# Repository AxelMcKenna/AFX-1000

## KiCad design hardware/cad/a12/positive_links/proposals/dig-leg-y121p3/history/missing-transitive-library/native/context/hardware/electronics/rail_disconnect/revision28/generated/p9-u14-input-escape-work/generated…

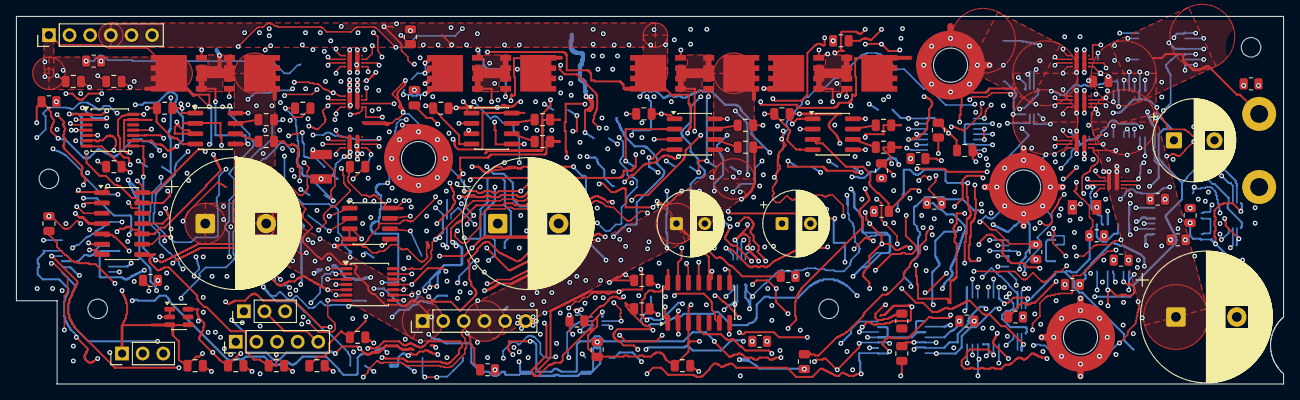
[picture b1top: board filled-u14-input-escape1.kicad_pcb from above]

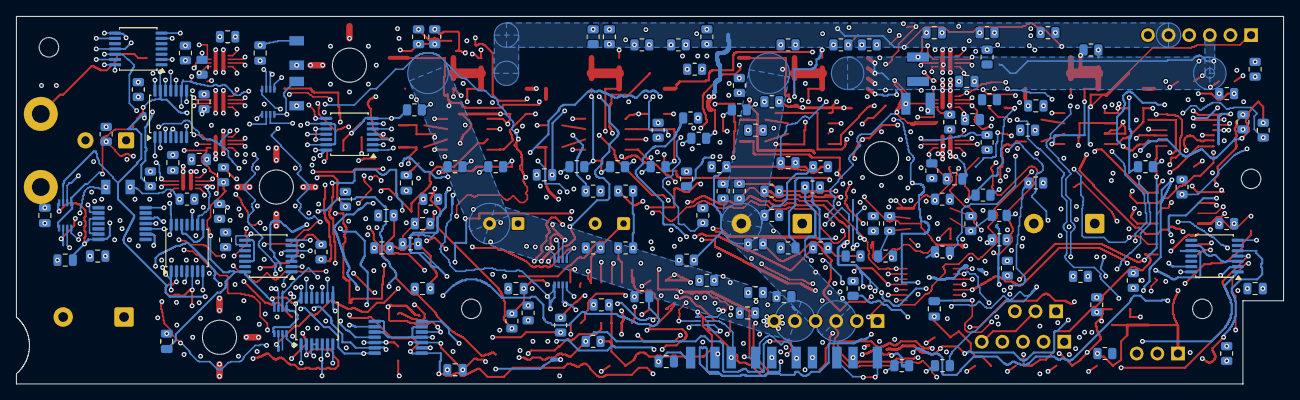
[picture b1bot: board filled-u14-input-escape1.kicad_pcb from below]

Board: 6 copper layers, 156.0 x 45.2 mm, 255 parts (151 on the bottom side), 174 nets.

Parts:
C1, C5, C9, C13, C17, C21, C25, C29, C34, C35, C36, C37, C57, C58, C59, C66, C67, C68, C69, C70, C71, C72, C73, C74, C75, C76, C77: 100nF 16V X7R; C_0805_2012Metric
C2, C3, C6, C7, C10, C11, C14, C15: 10pF 100V C0G 5%; C_0805_2012Metric
C4, C8: 1500uF 35V electrolytic 20% EEUFR1V152S; CP_Radial_D16.0mm_P7.50mm
C12, C16: 220uF 35V electrolytic 20% EEUFR1V221; CP_Radial_D8.0mm_P3.50mm
C20: 1500uF 16V electrolytic 20% EEUFR1C152; CP_Radial_D10.0mm_P5.00mm
C24: 4700uF 16V electrolytic 20% EEUFR1C472; CP_Radial_D16.0mm_P7.50mm
C26: 1uF 16V X7R; C_0805_2012Metric
C27, C28, C30, C31, C32, C33, C53, C54, C55, C56: 100pF 50V C0G 5%; C_0805_2012Metric
C38: 10uF 16V X7R; C_0805_2012Metric
C39, C41, C49, C61, C62, C63, C64, C65: 100nF 50V C0G 5% C1210C104J5GACTU; KEMET_C1210_LevelB
C40, C42, C44, C46, C48, C50, C52: 1uF 50V X7R; C_0805_2012Metric
C43, C45, C47, C51: 47nF 50V C0G 5% C1206C473J5GACTU; KEMET_C1206_LevelB
C60: 10nF 50V C0G 5%; C_0805_2012Metric
H1, H2, H3, H4: M2_CLEARANCE; M2_Clearance
J1, J3: Header6; PinHeader_1x06_P2.54mm_Vertical
J4: Alpha3079_AWG14_DIG_FORCE; AWG14_Force_2x1_P9mm_Engineering
J5, J6: Header3; PinHeader_1x03_P2.54mm_Vertical
J7, J8, J10, J11: 7466003R; 7466003R_M3_SMT_Annulus_NPTH
J9: E28 CONTROL; PinHeader_1x05_P2.54mm_Vertical
Q1, Q2, Q3, Q4, Q5, Q6, Q7, Q8: CSD18540Q5B; CSD18540Q5B_TI_Q5B
R1, R9, R17, R25: 22 1%; R_0805_2012Metric
R2, R10, R18, R26, R60, R63, R68, R71, R76, R81, R86, R91: 20M 1%; R_0805_2012Metric
R3, R5, R11, R13, R19, R21, R27, R29, R61, R64, R69, R72, R77, R82, R87, R92, R93: 10k 1%; R_0805_2012Metric
R4, R12, R20, R28, R98, R102, R106, R110, R114, R118, R122: 100 1%; R_0805_2012Metric
R6, R7, R14, R15, R22, R23, R30, R31: 15k 1%; R_0805_2012Metric
R8, R16, R24, R32, R40, R48: 47k 1%; R_0805_2012Metric
R49: 150k 0.01% 5ppm; R_0805_2012Metric
R50: 6.2k 0.01% 5ppm; R_0805_2012Metric
R51, R54, R58, R59, R62, R66, R67, R70, R74, R75, R79, R80, R84, R85, R89, R90, R94, R124, R127, R130, R133: 10k 0.01% 5ppm; R_0805_2012Metric
R52, R55: 1k 1%; R_0805_2012Metric
R53: 100k 0.01% 5ppm; R_0805_2012Metric
R56: 143k 0.01% 5ppm; R_0805_2012Metric
R57: 3.3k 0.01% 5ppm; R_0805_2012Metric
R65: 90.9k 0.01% 5ppm; R_0805_2012Metric
R73, R78: 31.6k 0.01% 5ppm; R_0805_2012Metric
R83: 12.4k 0.01% 5ppm; R_0805_2012Metric
R88: 7.5k 0.01% 5ppm; R_0805_2012Metric
R95, R99, R103, R107, R111, R115, R119, R125, R128, R131, R134, R136, R141: 10k; R_0805_2012Metric
R96, R100, R104, R108, R112, R116, R120, R140: 47k; R_0805_2012Metric
R97, R101, R117: 2.43k 0.1%; R_0805_2012Metric
R105, R109, R113, R121: 604 0.1%; R_0805_2012Metric
R123, R126, R129, R132: 28.7k 0.01% 5ppm; R_0805_2012Metric
R135: 100k; R_0805_2012Metric
R137: 11.1k 0.1%; R_0805_2012Metric
R138: 39.2 0.1%; R_0805_2012Metric
R139: 10k 0.1%; R_0805_2012Metric
R142: 15k; R_0805_2012Metric
U1, U2, U3, U4: SI8751AB-ISR; SOIC-8_3.9x4.9mm_P1.27mm
U7: REF35125QDBVR; SOT-23-6
U8: OPA2333AID; SOIC-8_3.9x4.9mm_P1.27mm
U9, U10: TLV1824DR; SOIC-14_3.9x8.7mm_P1.27mm
U11, U12, U24, U25, U26, U27: SN74LVC08APWR; TSSOP-14_4.4x5mm_P0.65mm
U13, U14, U15, U16, U17, U32, U33: TPS259482LYWP; TPS259482L_YWP0012A
U18: TLV1824PWR; TLV1824_PW0014A
U19, U20: TPS389001DSET; TPS389001_DSE0006A
U21, U22: SN74LVC02APWR; TSSOP-14_4.4x5mm_P0.65mm
U23: SN74LVC32APWR; TSSOP-14_4.4x5mm_P0.65mm
U28: SN74LVC14APWR; SN74LVC14A_PW0014A
U29, U30, U31, U34: SN74AUP2G08DCUR; SN74AUP2G08_DCU0008A

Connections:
/5V_DIG: C24.1, J4.1, R48.1, R132.1, U15.6, U15.11, U16.6, U16.11, U17.6, U17.11, U33.6, U33.11
/5V_DIG_OV_OK: R81.1, R82.2, U10.1, U11.10
/5V_DIG_OV_REF: R80.2, R81.2, U10.7
/5V_DIG_OV_SENSE: C33.1, R78.2, R79.1, U10.6
/5V_DIG_SRC: C44.1, C46.1, C48.1, C52.1, J11.1, R78.1, R126.1, U15.5, U15.12, U16.5, U16.12, U17.5, U17.12, U33.5, U33.12
/AGND: C1.2, C4.2, C5.2, C8.1, C9.2, C12.2, C13.2, C16.1, C17.2, C20.2, C21.2, C24.2, C25.2, C26.2, C27.2, C28.2, C29.2, C30.2, C31.2, C32.2, C33.2, C34.2, C35.2, C36.2, C37.2, C38.2, C39.2, C40.2, C41.2, C42.2, C43.2, C44.2, C45.2, C46.2, C47.2, C48.2, C49.2, C50.2, C51.2, C52.2, C53.2, C54.2, C55.2, C56.2, C57.2, C58.2, C59.2, C60.2, C61.2, C62.2, C63.2, C64.2, C65.2, C66.2, C67.2, C68.2, C69.2, C70.2, C71.2, C72.2, C73.2, C74.2, C75.2, C76.2, C77.2, J1.2, J3.2, J4.2, J5.2, J6.1, J7.1, J8.1, J9.1, R3.2, R5.2, R8.2, R11.2, R13.2, R16.2, R19.2, R21.2, R24.2, R27.2, R29.2, R32.2, R40.2, R48.2, R58.2, R66.2, R74.2, R79.2, R84.2, R89.2, R93.2, R94.2, R96.2, R97.2, R100.2, R101.2, R104.2, R105.2, R108.2, R109.2, R112.2, R113.2, R116.2, R117.2, R120.2, R121.2, R124.2, R127.2, R130.2, R133.2, R139.2, R140.2, R141.2, R142.2, U1.4, U2.4, U3.4, U4.4, U7.1, U7.2, U8.3, U8.4, U8.5, U9.12, U10.12, U11.7, U12.7, U13.2, U13.4, U13.8, U14.2, U14.4, U14.8, U15.2, U15.4, U15.8, U16.2, U16.4, U16.8, U17.2, U17.4, U17.8, U18.12, U19.2, U20.2, U21.7, U22.7, U22.9, U22.12, U23.7, U24.7, U25.4, U25.5, U25.7, U26.7, U27.7, U28.7, U29.4, U30.4, U31.4, U32.2, U32.4, U32.8, U33.2, U33.4, U33.8, U34.4
/ALL_RAILS_ALLOW: U12.11, U21.2, U29.1
/ANA_OUTPUT_OK: R131.2, U18.14, U24.4
/ANA_PG0: R95.1, U13.3, U31.2
/ANA_PG1: R99.1, U14.3, U34.6
/ANA_PG2: R115.1, U26.10, U32.3
/ANA_SOURCE_OK: R125.2, U18.2, U24.1
/DIG_OUTPUT_OK: R134.2, U18.13, U24.5
/DIG_PG0: R103.1, U15.3, U29.6
/DIG_PG1: R107.1, U16.3, U30.2
/DIG_PG2: R111.1, U17.3, U34.2
/DIG_PG3: R119.1, U26.9, U30.6, U33.3
/DIG_SOURCE_OK: R128.2, U18.1, U24.2
/E28_ALL_CHANNELS_READY: U26.8, U26.12
/E28_ANA_0_DVDT: R98.1, U13.7
/E28_ANA_0_DVDT_CAP: C39.1, R98.2
/E28_ANA_0_ILM: R97.1, U13.9
/E28_ANA_1_DVDT: R102.1, U14.7
/E28_ANA_1_DVDT_CAP: C41.1, R102.2
/E28_ANA_1_ILM: R101.1, U14.9
/E28_ANA_2_DVDT: R118.1, U32.7
/E28_ANA_2_DVDT_CAP: C49.1, R118.2
/E28_ANA_2_ILM: R117.1, U32.9
/E28_ANA_ENABLE: R96.1, U13.1, U30.3
/E28_ANA_FOLLOW: R100.1, U14.1, U31.7
/E28_ANA_FOLLOW2: R116.1, U32.1, U34.3
/E28_ANA_OUT_SENSE: C55.1, R129.2, R130.1, U18.9
/E28_ANA_SRC_SENSE: C53.1, R123.2, R124.1, U18.5
/E28_ARMED: U21.3, U21.4, U25.9
/E28_ARM_BAR: U21.1, U21.6
/E28_AUX_CT: C60.1, U19.5
/E28_AUX_DIV: R137.2, R138.1
/E28_AUX_RESET_N: R135.1, U19.6, U31.5
/E28_AUX_SENSE: R138.2, R139.1, U19.1
/E28_AUX_VALID: U24.13, U28.3, U29.2, U31.3
/E28_DIG_0_DVDT: R106.1, U15.7
/E28_DIG_0_DVDT_CAP: C43.1, R106.2
/E28_DIG_0_ILM: R105.1, U15.9
/E28_DIG_1_DVDT: R110.1, U16.7
/E28_DIG_1_DVDT_CAP: C45.1, R110.2
/E28_DIG_1_ILM: R109.1, U16.9
/E28_DIG_2_DVDT: R114.1, U17.7
/E28_DIG_2_DVDT_CAP: C47.1, R114.2
/E28_DIG_2_ILM: R113.1, U17.9
/E28_DIG_3_DVDT: R122.1, U33.7
/E28_DIG_3_DVDT_CAP: C51.1, R122.2
/E28_DIG_3_ILM: R121.1, U33.9
/E28_DIG_FOLLOW1: R108.1, U16.1, U29.3
/E28_DIG_FOLLOW2: R112.1, U17.1, U30.7
/E28_DIG_FOLLOW3: R120.1, U33.1, U34.7
/E28_DIG_OUT_SENSE: C56.1, R132.2, R133.1, U18.11
/E28_DIG_SRC_SENSE: C54.1, R126.2, R127.1, U18.7
/E28_FAULT: J9.4, U21.9, U21.13, U23.5, U28.5
/E28_FAULT_A: U23.8, U23.12
/E28_FAULT_ANY: U23.11, U25.10
/E28_FAULT_BAR: U21.10, U21.12
/E28_FAULT_SET: U21.8, U25.8
/E28_MASTER_ENABLE: J6.2, J9.5, R4.1, R12.1, R20.1, R28.1, R104.1, R141.1, U15.1, U20.1, U20.3, U25.13, U27.2, U29.5, U29.7, U30.1, U30.5, U31.1, U34.1, U34.5
/E28_NORMAL_OK: U22.8, U27.8
/E28_NORMAL_PRE: U24.8, U27.9
/E28_NOT_AUX: U23.2, U28.4
/E28_NOT_FAULT: U27.13, U28.6
/E28_NOT_NORMAL_OK: U22.10, U23.9
/E28_NOT_OUT_READY: U22.13, U26.2, U26.5
/E28_NOT_RUN: U23.1, U28.2, U28.9
/E28_NOT_SOURCE_READY: U28.10, U28.13
/E28_OUTPUT_PERMISSION: U26.11, U27.1
/E28_OUTPUT_READY: J9.3, U27.3
/E28_OUT_ARMED: U22.3, U22.4, U26.1
/E28_OUT_ARM_BAR: U22.1, U22.6
/E28_OUT_READY: U22.11, U24.6, U25.12, U26.13
/E28_OUT_UV_FAULT: U23.10, U26.3
/E28_OUT_VALID_ACTIVE: U22.2, U25.11
/E28_RESET: U21.5, U21.11, U23.3, U23.4
/E28_RESET_OUT: U22.5, U23.6
/E28_RUN_AND_SOURCE: U24.12, U27.6
/E28_RUN_LOGIC: U27.4, U28.8
/E28_SAFE_REQUEST: R140.1, U12.13, U27.11
/E28_SAFE_STAGE: U25.3, U27.12
/E28_SOURCE_READY: U24.3, U24.9, U25.2
/E28_SOURCE_READY_LOGIC: U27.5, U27.10, U28.12
/E28_TIMEOUT: R136.1, U20.6, U26.4
/E28_TIMEOUT_CT: C61.1, C62.1, C63.1, C64.1, C65.1, U20.5
/E28_TIMEOUT_FAULT: U23.13, U26.6
/E28_USER_AUX: U24.11, U25.1
/N12: C16.2, J3.5, Q8.3, R31.1, R32.1
/N12_ALLOW: R28.2, R29.1, U4.3
/N12_COMMON: Q7.1, Q8.1, R26.2, U4.5
/N12_DRIVE: R25.1, U4.8
/N12_GATE: Q7.2, Q8.2, R25.2, R26.1
/N12_INV: R54.1, R55.1, U8.7
/N12_MCAP1: C14.2, U4.7
/N12_MCAP1_LIMIT: C14.1, R30.2
/N12_MCAP2: C15.2, U4.6
/N12_MCAP2_LIMIT: C15.1, R31.2
/N12_OV_OK: R71.1, R72.2, U9.13, U11.5
/N12_OV_REF: R70.2, R71.2, U9.11
/N12_OV_SENSE: C28.1, R55.2, U9.10
/N12_SRC: J1.5, Q7.3, R30.1, R53.1
/N12_SUM: R53.2, R54.2, U8.6
/N12_TT: R27.1, U4.2
/N19: C8.2, J3.3, Q4.3, R15.1, R16.1
/N19_ALLOW: R12.2, R13.1, U2.3
/N19_COMMON: Q3.1, Q4.1, R10.2, U2.5
/N19_DRIVE: R9.1, U2.8
/N19_GATE: Q3.2, Q4.2, R9.2, R10.1
/N19_INPUT_MID: R49.2, R50.1
/N19_INV: R51.1, R52.1, U8.1
/N19_MCAP1: C6.2, U2.7
/N19_MCAP1_LIMIT: C6.1, R14.2
/N19_MCAP2: C7.2, U2.6
/N19_MCAP2_LIMIT: C7.1, R15.2
/N19_OV_OK: R63.1, R64.2, U9.1, U11.2
/N19_OV_REF: R62.2, R63.2, U9.7
/N19_OV_SENSE: C27.1, R52.2, U9.6
/N19_SRC: J1.3, Q3.3, R14.1, R49.1
/N19_SUM: R50.2, R51.2, U8.2
/N19_TT: R11.1, U2.2
/OK_5: U11.8, U12.4
/OK_12: U11.6, U12.2
/OK_19: U11.3, U12.1
/OK_ALL_OV: U12.8, U12.12, U24.10
/OK_ANALOG: U12.3, U12.9
/OK_AUXILIARY: U12.6, U12.10
/OK_REF: U11.11, U12.5
/P03_SOURCES_READY: J9.2, R142.1, U28.11
/P12: C12.1, J3.4, Q6.3, R23.1, R24.1
/P12_ALLOW: R20.2, R21.1, U3.3
/P12_COMMON: Q5.1, Q6.1, R18.2, U3.5
/P12_DRIVE: R17.1, U3.8
/P12_GATE: Q5.2, Q6.2, R17.2, R18.1
/P12_MCAP1: C10.2, U3.7
/P12_MCAP1_LIMIT: C10.1, R22.2
/P12_MCAP2: C11.2, U3.6
/P12_MCAP2_LIMIT: C11.1, R23.2
/P12_OV_OK: R68.1, R69.2, U9.14, U11.4
/P12_OV_REF: R67.2, R68.2, U9.9
/P12_OV_SENSE: C31.1, R65.2, R66.1, U9.8
/P12_SRC: J1.4, Q5.3, R22.1, R65.1
/P12_TT: R19.1, U3.2
/P19: C4.1, J3.1, Q2.3, R7.1, R8.1
/P19_ALLOW: R4.2, R5.1, U1.3
/P19_COMMON: Q1.1, Q2.1, R2.2, U1.5
/P19_DRIVE: R1.1, U1.8
/P19_GATE: Q1.2, Q2.2, R1.2, R2.1
/P19_MCAP1: C2.2, U1.7
/P19_MCAP1_LIMIT: C2.1, R6.2
/P19_MCAP2: C3.2, U1.6
/P19_MCAP2_LIMIT: C3.1, R7.2
/P19_OV_OK: R60.1, R61.2, U9.2, U11.1
/P19_OV_REF: R59.2, R60.2, U9.5
/P19_OV_SENSE: C30.1, R57.2, R58.1, U9.4
/P19_SENSE_MID: R56.2, R57.1
/P19_SRC: J1.1, Q1.3, R6.1, R56.1
/P19_TT: R3.1, U1.2
/POWER_RUN: J5.3, R93.1, U28.1
/PROTECT_REF: C26.1, J6.3, R59.1, R62.1, R67.1, R70.1, R75.1, R80.1, R85.1, R94.1, U7.6, U10.10, U18.4, U18.6, U18.8, U18.10
/REF_HIGH_AUX: R88.2, R89.1, R90.1
/REF_HIGH_OK: R91.1, R92.2, U10.13, U11.13
/REF_HIGH_POSITIVE: R90.2, R91.2, U10.11
/REF_LOW_AUX: R83.2, R84.1, U10.8
/REF_LOW_OK: R86.1, R87.2, U10.14, U11.12
/REF_LOW_POSITIVE: R85.2, R86.2, U10.9
/V2V5_AUX: C1.1, C5.1, C9.1, C13.1, C17.1, C21.1, C25.1, C29.1, C34.1, C35.1, C36.1, C37.1, C38.1, C57.1, C58.1, C59.1, C66.1, C67.1, C68.1, C69.1, C70.1, C71.1, C72.1, C73.1, C74.1, C75.1, C76.1, C77.1, J5.1, R61.1, R64.1, R69.1, R72.1, R77.1, R82.1, R83.1, R87.1, R88.1, R92.1, R95.2, R99.2, R103.2, R107.2, R111.2, R115.2, R119.2, R125.1, R128.1, R131.1, R134.1, R135.2, R136.2, R137.1, U1.1, U2.1, U3.1, U4.1, U7.3, U7.4, U8.8, U9.3, U10.3, U11.14, U12.14, U18.3, U19.3, U19.4, U20.4, U21.14, U22.14, U23.14, U24.14, U25.14, U26.14, U27.14, U28.14, U29.8, U30.8, U31.6, U31.8, U34.8
/V5_REG: C20.1, J3.6, R40.1, R129.1, U13.6, U13.11, U14.6, U14.11, U32.6, U32.11
/V5_REG_OV_OK: R76.1, R77.2, U10.2, U11.9
/V5_REG_OV_REF: R75.2, R76.2, U10.5
/V5_REG_OV_SENSE: C32.1, R73.2, R74.1, U10.4
/V5_REG_SRC: C40.1, C42.1, C50.1, J1.6, J10.1, R73.1, R123.1, U13.5, U13.12, U14.5, U14.12, U32.5, U32.12

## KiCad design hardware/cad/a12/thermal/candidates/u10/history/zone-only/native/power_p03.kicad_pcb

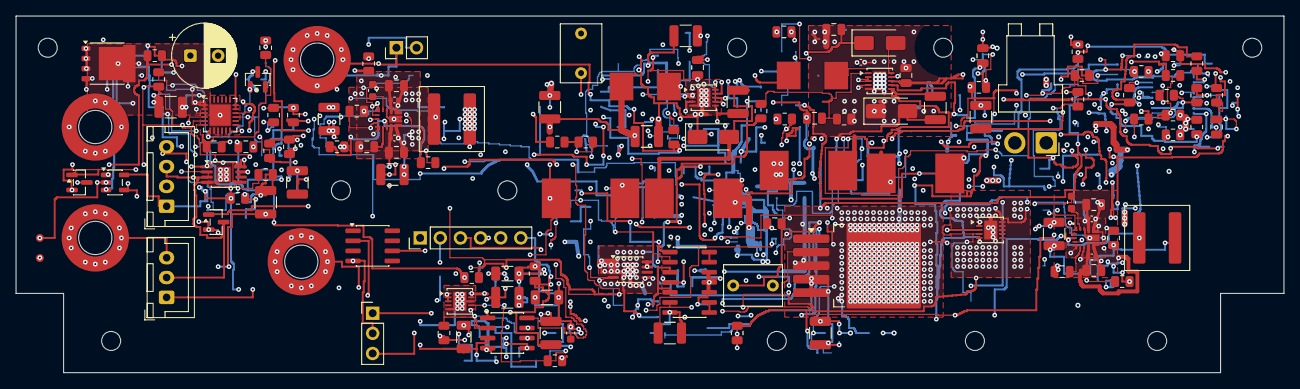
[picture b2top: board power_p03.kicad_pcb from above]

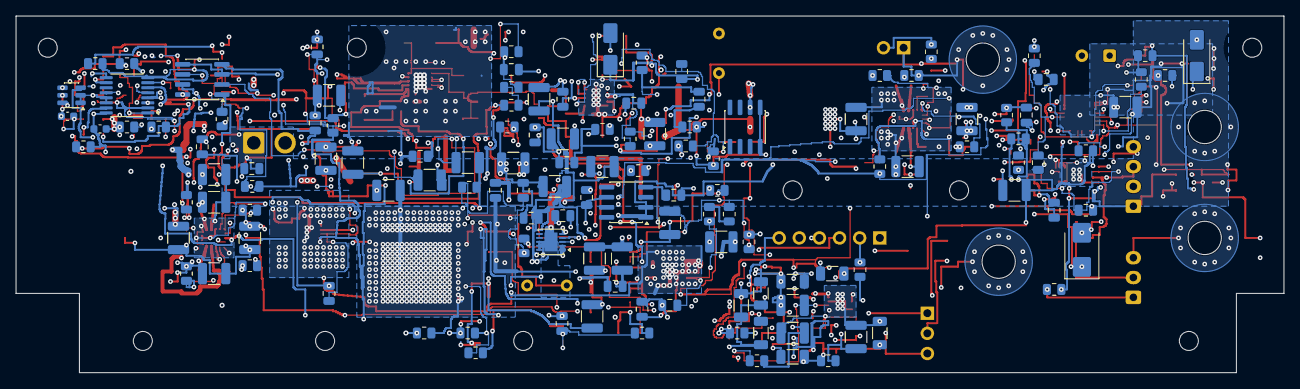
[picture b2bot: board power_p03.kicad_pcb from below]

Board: 6 copper layers, 160.0 x 45.0 mm, 265 parts (127 on the bottom side), 108 nets.

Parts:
C1, C63: 10uF 63V X7R; C_1210_3225Metric
C2, C3, C5, C6, C8, C9, C37, C42, C52, C57, C64, C65, C67, C68, C70, C204, C205, C224, C225, C254: 22uF 50V X7R 20% TDK C3225X7R1H226M250AC; C_1210_3225Metric
C4, C7, C10, C35, C38, C40, C43, C50, C53, C55, C58, C59, C61, C66, C69, C71: 100nF 50V X7R; C_0805_2012Metric
C11, C30, C107, C108: 100nF 16V X7R; C_0805_2012Metric
C12, C14, C73, C75: 68pF 50V C0G 5%; C_0805_2012Metric
C13, C15, C74, C76: 330nF 16V X7R; C_0805_2012Metric
C31: 2.2uF 16V X7R; C_0805_2012Metric
C32, C33: 1uF film 63V 10% MKS2C041001F00KSSD; C_Rect_L7.2mm_W5.0mm_P5.00mm
C34, C39, C49, C54, C240: 47nF 50V C0G 5%; C_1210_3225Metric
C36, C41, C51, C56: 10uF 50V X7R; C_1210_3225Metric
C60, C62, C105: 1uF 50V X7R; C_0805_2012Metric
C72, C210, C211, C230, C231: 100nF 50V X7R 10% TDK C1005X7R1H104K050BB; C_0402_1005Metric
C101, C102: 2.2uF 100V X7R; C_1210_3225Metric
C103: 220uF 35V electrolytic 20% (EEUFR1V221); CP_Radial_D8.0mm_P3.50mm
C104: 1uF 50V X7R; C_1210_3225Metric
C106: 10uF 16V X7R; C_1210_3225Metric
C109: 1nF 16V C0G 5%; C_0805_2012Metric
C110: 10nF 16V C0G 5%; C_0805_2012Metric
C200, C220: 4.7uF 25V X7R 10% TDK C2012X7R1E475K125AB; C_0805_2012Metric
C201, C221, C255, C301, C302: 100nF 50V X7R; C_0603_1608Metric
C202, C203, C222, C223: 2.2uF 50V X7R 10% TDK C2012X7R1H225K125AC; C_0805_2012Metric
C206, C207, C208, C209, C226, C227, C228, C229: 47uF 25V X7S 20% TDK C3225X7S1E476M250AC; C_1210_3225Metric
C241: 1uF 25V X7R; C_1210_3225Metric
C242, C243, C244, C245, C246, C247, C248, C249, C250, C251: 100nF 25V C0G 5% KEMET C1206C104J3GACTU; C_1206_3216Metric
C252, C253: 1uF 16V X7R; C_1210_3225Metric
C300: 10nF 50V C0G 5%; C_0805_2012Metric
D1, D2, D3, D4, D103: SS16-E3/61T; D_SMA
D101: SMBJ33CA-E3/52; D_SMB
D102: BAS116,215; SOT-23
H1, H2, H3, H4, H5, H6, H7, H8, H9, H10: M2_CLEARANCE; M2_Clearance
J2: Header6; PinHeader_1x06_P2.54mm_Vertical
J3: Header2; PinHeader_1x02_P2.54mm_Vertical
J20, J21, J23, J24: Wurth 7466003R M3 SMT; Wurth_7466003R
J22: P03 READY test; PinHeader_1x03_P2.54mm_Vertical
J101: JST B2PS-VH (VHR-2N/SVH-41T-P1.1 AWG16); JST_VH_B2PS-VH_1x02_P3.96mm_Horizontal
J103: Bare POWER_READY probe pads, no fitted header; Probe2_P2.54_D1
J104: JST B3B-XH-A (XHP-3/SXH-001T-P0.6); JST_XH_B3B-XH-A_1x03_P2.50mm_Vertical
J106: JST B4B-XH-A (XHP-4/SXH-001T-P0.6); JST_XH_B4B-XH-A_1x04_P2.50mm_Vertical
L1, L6: 33uH 20% SRP7050WA-330M; SRP7050WA
L2, L3, L7, L8: 68uH 20% SRP1050WA-680M; SRP1050WA
L20, L23: 4.7uH 20% Coilcraft XAL7030-472MEC; L_Coilcraft_XAL7030-472
Q101: PSMN012-100YL,115; LFPAK56
Q102: BSS138-7-F; SOT-23
Q103: DMN2056U-7; SOT-23
R1: 300k 0.01% 5ppm; R_0805_2012Metric
R2, R3, R4, R45, R46: 15k 0.01% 5ppm; R_0805_2012Metric
R5, R20, R21, R34, R35: 330k 0.01% 5ppm; R_0805_2012Metric
R6, R7, R49, R50: 4.7k 1%; R_0805_2012Metric
R17, R19, R110: 1k 1%; R_0805_2012Metric
R18, R120: 100k 1%; R_0805_2012Metric
R22, R27, R36, R41, R243, R244: 100k 0.01% 5ppm; R_0805_2012Metric
R23, R28, R37, R42, R241: 6.8k 1%; R_0805_2012Metric
R24, R38: 9.09k 1%; R_0805_2012Metric
R25, R39, R47, R306: 200k 0.01% 5ppm; R_0805_2012Metric
R26, R40, R308: 180k 0.01% 5ppm; R_0805_2012Metric
R29, R43: 5.62k 1%; R_0805_2012Metric
R44: 240k 0.01% 5ppm; R_0805_2012Metric
R48, R301, R303, R305, R307, R309, R314: 10k 0.01% 5ppm; R_0805_2012Metric
R101, R103, R117: 309k 0.1% 10ppm; R_0805_2012Metric
R102: 40.2k 0.1% 10ppm; R_0805_2012Metric
R104: 28k 0.1% 10ppm; R_0805_2012Metric
R105: 68.1k 0.1% 10ppm; R_0805_2012Metric
R106, R109, R118, R119: 10k 0.1% 10ppm; R_0805_2012Metric
R107: 4.02k 0.1% 10ppm; R_0805_2012Metric
R108: 11.7k 0.1% 10ppm; R_0805_2012Metric
R111, R204, R224, R246: 10k 1%; R_0805_2012Metric
R112, R114: 47k 1%; R_0805_2012Metric
R113: 3.3k 1%; R_0805_2012Metric
R115: 30.9k 0.1% 10ppm; R_0805_2012Metric
R116: 3.09k 0.1% 10ppm; R_0805_2012Metric
R121: 100 1%; R_0805_2012Metric
R130: 49.9 0.01% 5ppm; R_0805_2012Metric
R200: 9k 0.01% 2ppm Susumu RG2012L-902-L-T1; R_0805_2012Metric
R201: 1k 0.01% 2ppm Susumu RG2012L-102-L-T1; R_0805_2012Metric
R202, R222: 24.3k 1%; R_0805_2012Metric
R203, R223: 18.2k 0.1% 25ppm Panasonic ERA6AEB1822V; R_0805_2012Metric
R205, R225: 22k 1%; R_0805_2012Metric
R206: 54.9 0.1% 25ppm Panasonic ERA6AEB549V; R_0805_2012Metric
R220: 11k 0.01% 5ppm; R_0805_2012Metric
R221, R311: 1k 0.01% 5ppm; R_0805_2012Metric
R240: 100 0.01% 5ppm; R_0805_2012Metric
R242: 120 0.01% 5ppm; R_0805_2012Metric
R245: 2.21k 1%; R_0805_2012Metric
R300, R302: 87.6k 0.01% 5ppm; R_0805_2012Metric
R304: 324k 0.01% 5ppm; R_0805_2012Metric
R310: 590 0.01% 5ppm; R_0805_2012Metric
R312: 7.5k 0.01% 5ppm; R_0805_2012Metric
R313: 1M 0.01% 5ppm; R_0805_2012Metric
R315: 750k 0.01% 5ppm; R_0805_2012Metric
R316: 2.2k 0.1% 25ppm Panasonic ERA6AEB222V; R_0805_2012Metric
U1, U13: LT3471EDD#PBF; DFN-10-1EP_3x3mm_P0.5mm_EP1.65x2.38mm
U4: REF5025EIDR; SOIC-8_3.9x4.9mm_P1.27mm
U5: OPA4192ID; SOIC-14_3.9x8.7mm_P1.27mm
U6, U24: OPA2192ID; SOIC-8_3.9x4.9mm_P1.27mm
U7: LT3080IMS8E#PBF; MSOP-8-1EP_3x3mm_P0.65mm_EP1.68x1.88mm
U8: LT3080IQ#PBF; TO-263-5_TabPin3
U10, U11: LT3090IDD#PBF; DFN-10-1EP_3x3mm_P0.5mm_EP1.65x2.38mm
U12: LT1634AIS8-2.5#PBF; SOIC-8_3.9x4.9mm_P1.27mm
U20, U23: TPS543620RPYR; TPS543620_RPY0014A
U21: ADR4550BRZ; SOIC-8_3.9x4.9mm_P1.27mm
U22: LT3045IDD#PBF; DFN-10-1EP_3x3mm_P0.5mm_EP1.65x2.38mm
U25: LTC2910HGN#PBF; SSOP-16_3.9x4.9mm_P0.635mm
U26: SN74LVC1G97DBVR; SOT-23-6
U101: TPS26630RGER; Texas_RGE0024H_VQFN-24-1EP_4x4mm_P0.5mm_EP2.7x2.7mm
U102: TPS7A1601DGNR; MSOP-8-1EP_3x3mm_P0.65mm_EP1.68x1.88mm
U103: TLV7011DBVR; SOT-23-5

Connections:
/5V_DIG_SRC: C30.1, C206.1, C207.1, C208.1, C209.1, J3.1, J23.1, L20.2, R6.1, R7.1, R49.1, R50.1, R200.1, R300.1, U4.1, U4.2, U10.5, U11.5
/AGND: C2.2, C3.2, C4.2, C5.2, C6.2, C7.2, C8.2, C9.2, C10.2, C11.2, C13.2, C15.2, C30.2, C31.2, C32.2, C33.2, C35.2, C36.2, C37.2, C38.2, C40.2, C41.2, C42.2, C43.2, C50.2, C51.2, C52.2, C53.2, C55.2, C56.2, C57.2, C58.2, C59.2, C60.2, C61.2, C62.2, C64.2, C65.2, C66.2, C67.2, C68.2, C69.2, C70.2, C71.2, C72.2, C74.2, C76.2, C101.2, C102.2, C103.2, C104.2, C105.2, C106.2, C107.2, C108.2, C109.2, C110.2, C200.2, C202.2, C203.2, C204.2, C205.2, C206.2, C207.2, C208.2, C209.2, C210.2, C211.2, C220.2, C222.2, C223.2, C224.2, C225.2, C226.2, C227.2, C228.2, C229.2, C230.2, C231.2, C241.2, C242.2, C243.2, C244.2, C245.2, C246.2, C247.2, C248.2, C249.2, C250.2, C251.2, C252.2, C253.2, C254.2, C255.2, C300.2, C301.2, C302.2, D2.1, D4.1, D101.2, D103.2, J2.2, J3.2, J20.1, J21.1, J22.2, J101.2, J103.1, J104.3, J106.2, Q103.2, R3.2, R22.2, R24.2, R27.2, R29.2, R36.2, R38.2, R41.2, R43.2, R45.2, R102.2, R104.2, R106.2, R107.2, R109.2, R111.2, R112.2, R114.2, R116.2, R119.2, R120.2, R201.2, R202.2, R203.2, R205.2, R221.2, R222.2, R223.2, R225.2, R243.2, R245.2, R301.2, R303.2, R305.2, R307.2, R309.2, R311.2, U1.5, U1.11, U4.4, U5.10, U5.11, U5.12, U6.8, U10.3, U11.3, U12.6, U13.5, U13.11, U20.5, U20.9, U20.11, U21.4, U22.5, U22.8, U22.11, U23.5, U23.9, U23.11, U24.4, U24.5, U25.9, U25.13, U25.14, U26.1, U26.2, U101.8, U101.25, U102.4, U102.9, U103.2
/AUX_FB: R109.1, R130.2, U102.2
/AUX_START_DELAY: C110.1, U102.7
/BLOCK_DRV: Q102.1, U101.4
/BLOCK_GATE: Q101.4, Q102.3, U101.3
/CUK_NODE: C1.2, D2.2, L3.1
/DC_IN: C101.1, D101.1, J101.1, Q101.1, Q101.2, Q101.3, Q102.2, R101.1, R103.1, U101.5
/FAST_OV_GATE: Q103.1, R120.1, R121.2
/FAST_OV_OUT: R117.1, R121.1, U103.1
/FAST_OV_REF: C109.1, R118.2, R119.1, U103.4
/FAST_OV_SENSE: R115.2, R116.1, R117.2, U103.3
/INPUT_ILIM: R107.1, U101.10
/INPUT_OV: D102.1, R103.2, R104.1, U101.7
/INPUT_PGTH: R105.2, R106.1, U101.15
/INPUT_SLEW: C105.1, U101.9
/INPUT_UV: R101.2, R102.1, U101.6
/LO_CUK_NODE: C63.2, D4.2, L8.1
/LO_N_FB: C75.2, R46.2, R47.1, U13.4
/LO_N_RMID: R47.2, R48.1
/LO_N_SS: C76.1, R50.2, U13.7
/LO_N_SW: C63.1, L7.2, U13.6
/LO_P_FB: C73.2, R44.2, R45.1, U13.1
/LO_P_SS: C74.1, R49.2, U13.9
/LO_P_SW: D3.2, L6.2, U13.10
/LO_REF_1V: C72.1, R46.1, U13.2, U13.3
/N12_DRIVE: C54.1, R42.1, U6.7
/N12_FB: C54.2, R40.2, R41.1, U6.6
/N12_RMID: R39.2, R40.1
/N12_SET: C55.1, R39.1, R42.2, U11.4
/N12_SRC: C57.1, C58.1, J2.5, R43.1, R315.2, U11.1, U11.2
/N19_DRIVE: C49.1, R37.1, U6.1
/N19_FB: C49.2, R35.2, R36.1, U6.2
/N19_RMID: R34.2, R35.1
/N19_SET: C50.1, R34.1, R37.2, U10.4
/N19_SRC: C52.1, C53.1, J2.3, R38.1, R313.2, U10.1, U10.2
/NREF_2V5: R18.1, R19.1, U12.4, U12.5
/NREF_FILTER: C33.1, R19.2, U6.3, U6.5
/P03_ALL_SOURCES_READY: J22.1, J106.4, R316.2, U25.12
/P03_ANA_DIV: R242.2, R243.1, R244.1
/P03_ANA_DRIVE: C240.1, R241.1, U24.1
/P03_ANA_FB: C240.2, R244.2, U24.2
/P03_ANA_SET: C241.1, R241.2, R242.1, U22.7
/P03_AUX_TRIM: R108.2, R130.1
/P03_A_BOOT: C221.1, U23.14
/P03_A_BP5: C220.1, U23.6
/P03_A_ENABLE: R224.2, R225.1, U23.7
/P03_A_FB: R220.2, R221.1, U23.4
/P03_A_FSEL: R222.1, U23.1
/P03_A_MODE: R223.1, U23.2
/P03_A_SW: C221.2, L23.1, U23.10, U23.13
/P03_D_BOOT: C201.1, U20.14
/P03_D_BP5: C200.1, U20.6
/P03_D_ENABLE: R204.2, R205.1, U20.7
/P03_D_FB: R201.1, R206.2, U20.4
/P03_D_FB_TRIM: R200.2, R206.1
/P03_D_FSEL: R202.1, U20.1
/P03_D_MODE: R203.1, U20.2
/P03_D_SW: C201.2, L20.1, U20.10, U20.13
/P03_MON_ANA: R302.2, R303.1, U25.2
/P03_MON_BUCK_OK: U25.5, U26.4
/P03_MON_DIG: R300.2, R301.1, U25.1
/P03_MON_N12: R314.2, R315.1, U25.8
/P03_MON_N19: R312.2, R313.1, U25.7
/P03_MON_NEG_BIAS: R310.2, R311.1, R312.1, R314.1
/P03_MON_P12: R306.2, R307.1, U25.4
/P03_MON_P19: R304.2, R305.1, U25.3
/P03_MON_REF: R310.1, U25.10
/P03_MON_TIMER: C300.1, U25.15
/P03_MON_VIN: R308.2, R309.1, U25.6
/P03_PRE6V: C226.1, C227.1, C228.1, C229.1, C253.1, L23.2, R220.1, U21.2, U22.1, U22.2, U22.3, U22.6
/P03_REF5: C252.1, R240.1, U21.6
/P03_REF_FILTER: C242.1, C243.1, C244.1, C245.1, C246.1, C247.1, C248.1, C249.1, C250.1, C251.1, R240.2, U24.3
/P03_SOURCES_READY: R246.2, U20.3, U23.3, U26.3
/P03_SPARE_24: U24.6, U24.7
/P03_SPARE_C: U5.8, U5.9
/P12_DRIVE: C39.1, R28.1, U5.7
/P12_FB: C39.2, R26.2, R27.1, U5.6
/P12_RMID: R25.2, R26.1
/P12_SET: C40.1, R25.1, R28.2, U8.2
/P12_SRC: C42.1, C43.1, J2.4, R29.1, R306.1, U8.3
/P19_DRIVE: C34.1, R23.1, U5.1
/P19_FB: C34.2, R21.2, R22.1, U5.2
/P19_RMID: R20.2, R21.1
/P19_SET: C35.1, R20.1, R23.2, U7.4
/P19_SRC: C37.1, C38.1, J2.1, R24.1, R304.1, U7.1, U7.2, U7.3, U7.9
/POWER_READY: J22.3, J103.2, R110.2, R204.1, R224.1, U26.6, U101.16
/POWER_RUN: J104.2, J106.3, Q103.3, R112.1, U101.12, U102.3
/PREF_2V5: C31.1, R17.1, U4.6
/PREF_FILTER: C32.1, R17.2, U5.3, U5.5
/RAW_N17: C56.1, C67.1, C68.1, C69.1, C75.1, L8.2, R48.2, U11.8, U11.9, U11.10, U11.11
/RAW_N22: C8.1, C9.1, C10.1, C14.1, C51.1, C61.1, C62.1, L3.2, R5.2, R18.2, U6.4, U10.8, U10.9, U10.10, U10.11
/RAW_N_FB: C14.2, R4.2, R5.1, U1.4
/RAW_N_SS: C15.1, R7.2, U1.7
/RAW_N_SW: C1.1, L2.2, U1.6
/RAW_P17: C41.1, C64.1, C65.1, C66.1, C73.1, D3.1, R44.1, U8.4, U8.5
/RAW_P22: C5.1, C6.1, C7.1, C12.1, C36.1, C59.1, C60.1, D1.1, R1.1, U5.4, U7.5, U7.7, U7.8
/RAW_P_FB: C12.2, R2.2, R3.1, U1.1
/RAW_P_RMID: R1.2, R2.1
/RAW_P_SS: C13.1, R6.2, U1.9
/RAW_P_SW: D1.2, L1.2, U1.10
/SPARE_OUT: U5.13, U5.14
/SWITCH_SUPPLY: J104.1, R113.2
/SW_REF_1V: C11.1, R4.1, U1.2, U1.3
/V2V5_AUX: C106.1, C107.1, C108.1, C301.1, C302.1, D102.3, J106.1, R108.1, R110.1, R111.1, R113.1, R118.1, R246.1, R316.1, U25.16, U26.5, U102.1, U103.5
/V5_REG_SRC: C254.1, J2.6, J24.1, R245.1, R302.1, U22.9, U22.10
/VIN_IC: C102.1, Q101.5, R115.1, U101.1, U101.2, U102.5, U102.8
/VIN_PROTECTED: C2.1, C3.1, C4.1, C70.1, C71.1, C103.1, C104.1, C202.1, C203.1, C204.1, C205.1, C210.1, C211.1, C222.1, C223.1, C224.1, C225.1, C230.1, C231.1, C255.1, D103.1, L1.1, L2.1, L6.1, L7.1, R105.1, R114.1, R308.1, U1.8, U13.8, U20.8, U20.12, U23.8, U23.12, U24.8, U101.17, U101.18
